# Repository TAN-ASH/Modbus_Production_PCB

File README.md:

# Modbus_Production_PCB
Production utility for Liminal-K production

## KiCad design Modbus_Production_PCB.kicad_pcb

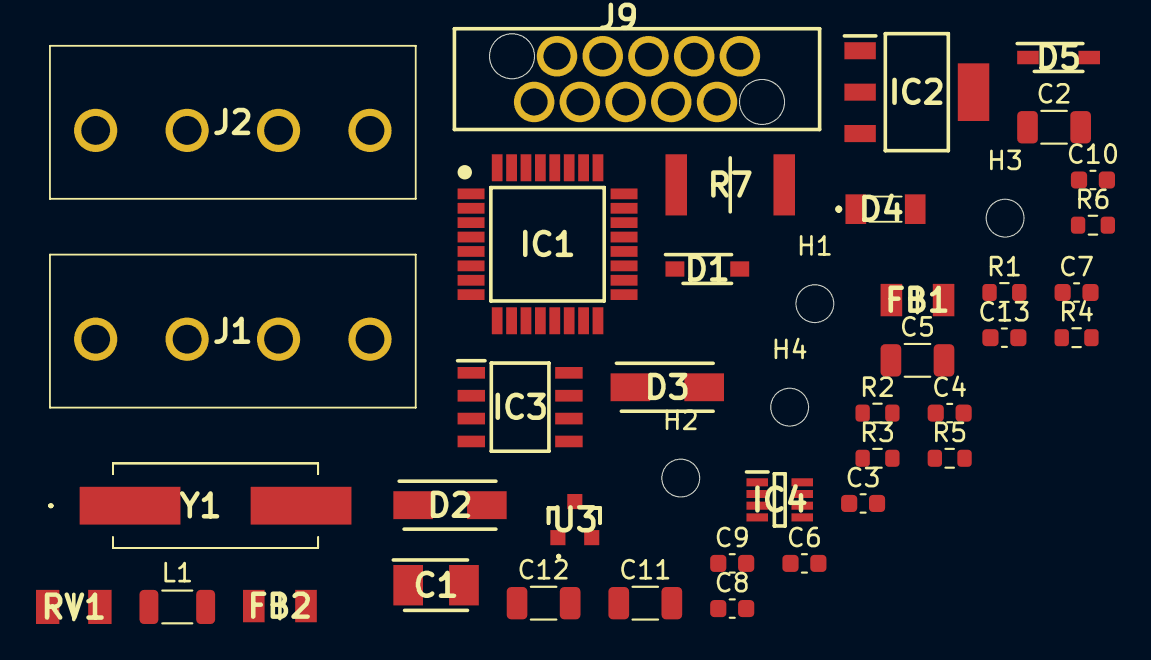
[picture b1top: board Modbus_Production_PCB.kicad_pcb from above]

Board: 2 copper layers, 42 parts (0 on the bottom side), 23 nets, no tracks yet.

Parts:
C1: 10uF35V; CAPPM3528X210N
C2: 0.1uF35V; C_1206_3216Metric
C3, C4, C9, C10: 100nF; C_0603_1608Metric
C5: 1uF; C_1206_3216Metric
C6: 10nF; C_0603_1608Metric
C7, C8: 22pF; C_0603_1608Metric
C11: 4.7uF10V; C_1206_3216Metric
C12: 4.7uF; C_1206_3216Metric
C13: 1uF; C_0603_1608Metric
D1: B5819W-TP; SOD3716X135N
D2, D3: D_TVS; DIOM5127X229N
D4: D; FDLL4448
D5: D_Zener; SOD3716X145N
FB1, FB2: 74279218; BEADC3216X130N
H1, H2, H3, H4: MountingHole; MountingHole_2.1mm
IC1: ATMEGA328PB-AN; QFP80P900X900X120-32N
IC2: TPS7B6933QDCYRQ1; SOT230P700X180-4N
IC3: MAX3072EASA+; SOIC127P600X175-8N
IC4: INA219BIDCNT; SOT65P280X145-8N
J1, J2: 691311500004
J9: 490107671012
L1: 10nH; L_1206_3216Metric
R1, R2, R3, R4, R5: 4K7; R_0603_1608Metric
R6: 100K; R_0603_1608Metric
R7: 0.1R; RESC6432X65N
RV1: Varistor; VARC3216X145N
U3: PSM712-LF-T7; PSM712LFT7
Y1: 7.37MHz; ABLS373728MHZD4YT

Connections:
+3V3: C5.1, C6.1, C9.1, C11.1, D4.1, FB2.2, IC1.4, IC2.3, IC4.4, J9.2, L1.1, R2.1, R3.1, R4.1, R5.1
+12V: IC4.1, J1.1, R7.2
/Data_A: D3.2, IC3.6, J1.4, J2.1, U3.1
/Data_B: D3.1, IC3.7, J1.3, J2.2, U3.2
/IN-: IC4.2, J2.4, R7.1
/MAX_EN: IC1.27, IC3.2, IC3.3
/MISO: IC1.16, J9.9
/MOSI: IC1.15, J9.1
/RSB: C13.1, D4.2, D5.1, IC1.29, J9.5, R5.2
/RXD: IC1.30, IC3.1, R2.2
/SCK: IC1.17, J9.7
/TXD: IC1.31, IC3.4
/Vin: IC1.22, R1.1, R6.2
GND: C1.2, C2.2, C3.2, C4.1, C5.2, C6.2, C7.2, C8.2, C9.2, C10.2, C11.2, C12.2, C13.2, D2.2, D5.2, IC1.5, IC1.21, IC2.2, IC2.4, IC3.5, IC4.3, IC4.7, IC4.8, J1.2, J2.3, J9.3, J9.8, J9.10, R1.2, RV1.2, U3.3
unnamed: C1.1, C2.1, FB1.2, IC2.1, R6.1
unnamed: C3.1, IC1.18, L1.2
unnamed: C4.2, IC1.20
unnamed: C7.1, IC1.8, Y1.2
unnamed: C8.1, IC1.7, Y1.1
unnamed: C10.1, C12.1, FB2.1, IC3.8
unnamed: D1.1, D2.1, FB1.1, RV1.1
SCL: IC1.6, IC4.5, R3.2
SDA: IC1.3, IC4.6, R4.2

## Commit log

2021-09-25 Post Production PCB inprogress
